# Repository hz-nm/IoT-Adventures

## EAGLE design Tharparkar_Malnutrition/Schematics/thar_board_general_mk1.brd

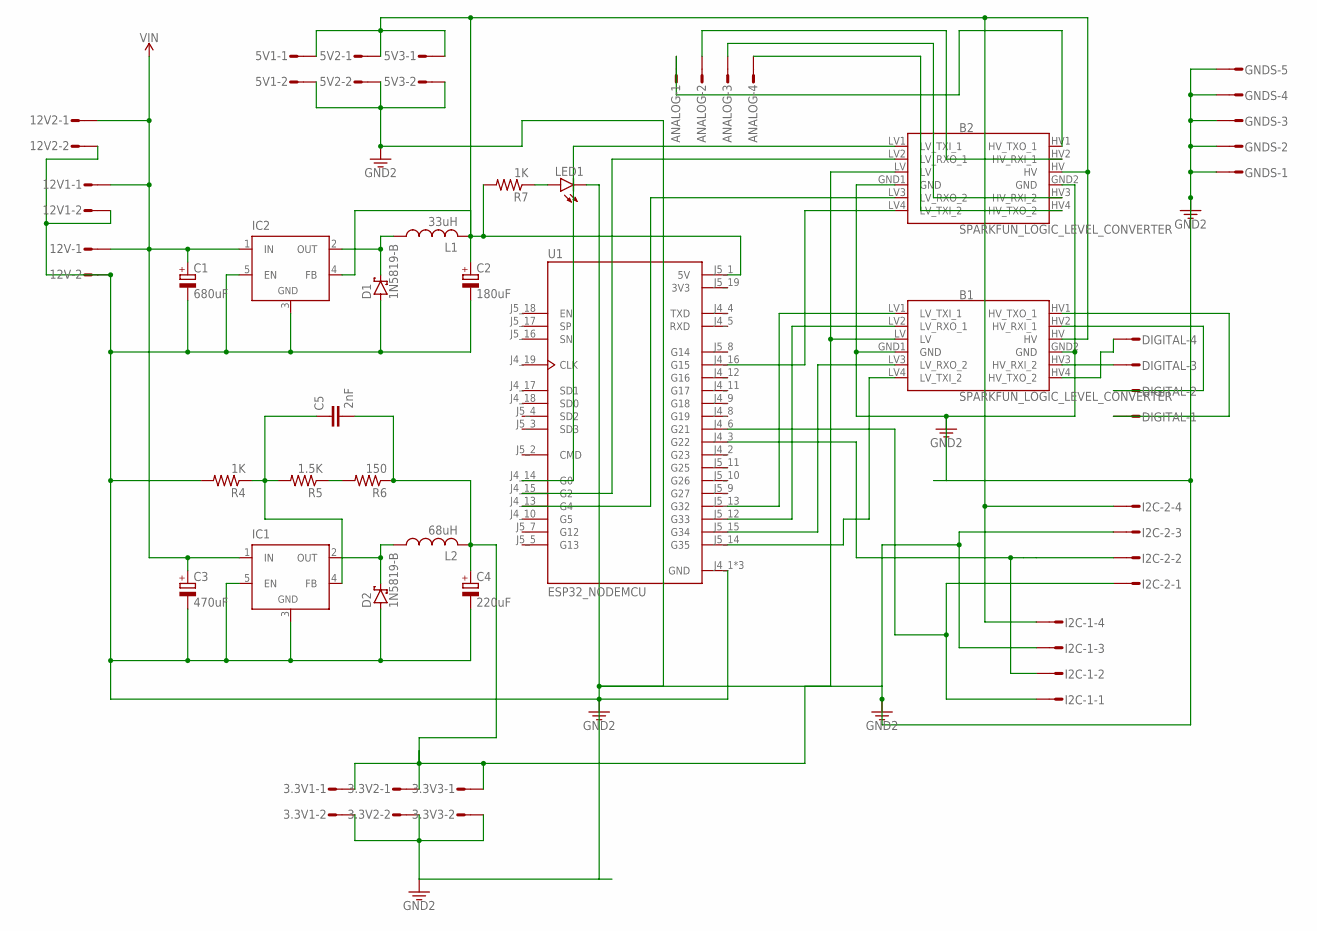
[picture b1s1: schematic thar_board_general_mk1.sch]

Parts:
3.3V1, 3.3V2, 3.3V3, 5V1, 5V2, 5V3, 12V, 12V1, 12V2: L02P
ANALOG: L04P
B1, B2: SPARKFUN_LOGIC_LEVEL_CONVERTER
C1: 680uF; E2,5-7
C2: 180uF; E2,5-7
C3: 470uF; E2,5-7
C4: 220uF; E2,5-7
C5: 2nF; C025-025X050
D1, D2: 1N5819-B; DO41-7.6
DIGITAL: L04P
GNDS: L05P
I2C-1, I2C-2: L04P
IC1, IC2: LM2596TH; TO220-52
L1: 33uH; TFI0410
L2: 68uH; TFI0410
LED1: LED3MM
R4, R7: 1K; 0207/10
R5: 1.5K; 0207/10
R6: 150; 0207/10
U1: ESP32_NODEMCU; MODULE_ESP32_NODEMCU

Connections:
3V3: U1.J5_19 (3V3)
5V: 5V1.1, 5V2.1, 5V3.1, B1.HV, B2.HV, C2.+, I2C-1.4, I2C-2.4, IC2.4 (FB), L1.2, R7.2, U1.J5_1 (5V)
5V1: 3.3V1.1, 3.3V2.1, 3.3V3.1, B1.LV, B2.LV, C4.+, C5.2, L2.2, R6.1
DLETE: B2.LV1 (LV_TXI_1), U1.J4_14 (G0)
GND: 3.3V1.2, 3.3V2.2, 3.3V3.2, 5V1.2, 5V2.2, 5V3.2, 12V.2, 12V1.2, 12V2.2, B1.GND1 (GND), B1.GND2 (GND), B2.GND1 (GND), B2.GND2 (GND), C1.-, C2.-, C3.-, C4.-, D1.A, D2.A, GNDS.1, GNDS.2, GNDS.3, GNDS.4, GNDS.5, I2C-1.3, I2C-2.3, IC1.3 (GND), IC1.5 (EN), IC2.3 (GND), IC2.5 (EN), LED1.K (C), R4.2, U1.J4_1 (GND), U1.J4_7 (GND), U1.J5_6 (GND)
unnamed: LED1.A, R7.1
unnamed: B2.LV4 (LV_TXI_2), U1.J4_16 (G15)
unnamed: B1.HV1 (HV_TXO_1), DIGITAL.1
unnamed: B2.LV2 (LV_RXO_1), U1.J4_15 (G2)
unnamed: D1.C, IC2.2 (OUT), L1.1
unnamed: B2.LV3 (LV_RXO_2), U1.J4_13 (G4)
unnamed: ANALOG.1, B2.HV1 (HV_TXO_1)
unnamed: D2.C, IC1.2 (OUT), L2.1
unnamed: ANALOG.4, B2.HV4 (HV_TXO_2)
unnamed: ANALOG.3, B2.HV3 (HV_RXI_2)
unnamed: ANALOG.2, B2.HV2 (HV_RXI_1)
unnamed: B1.LV1 (LV_TXI_1), U1.J5_13 (G32)
unnamed: C5.1, IC1.4 (FB), R4.1, R5.2
unnamed: B1.LV2 (LV_RXO_1), U1.J5_12 (G33)
unnamed: R5.1, R6.2
unnamed: B1.LV3 (LV_RXO_2), U1.J5_15 (G34)
unnamed: B1.LV4 (LV_TXI_2), U1.J5_14 (G35)
unnamed: B1.HV2 (HV_RXI_1), DIGITAL.2
unnamed: B1.HV3 (HV_RXI_2), DIGITAL.3
unnamed: B1.HV4 (HV_TXO_2), DIGITAL.4
SCL: I2C-1.2, I2C-2.2, U1.J4_3 (G22)
SDA: I2C-1.1, I2C-2.1, U1.J4_6 (G21)
VIN: 12V.1, 12V1.1, 12V2.1, C1.+, C3.+, IC1.1 (IN), IC2.1 (IN)

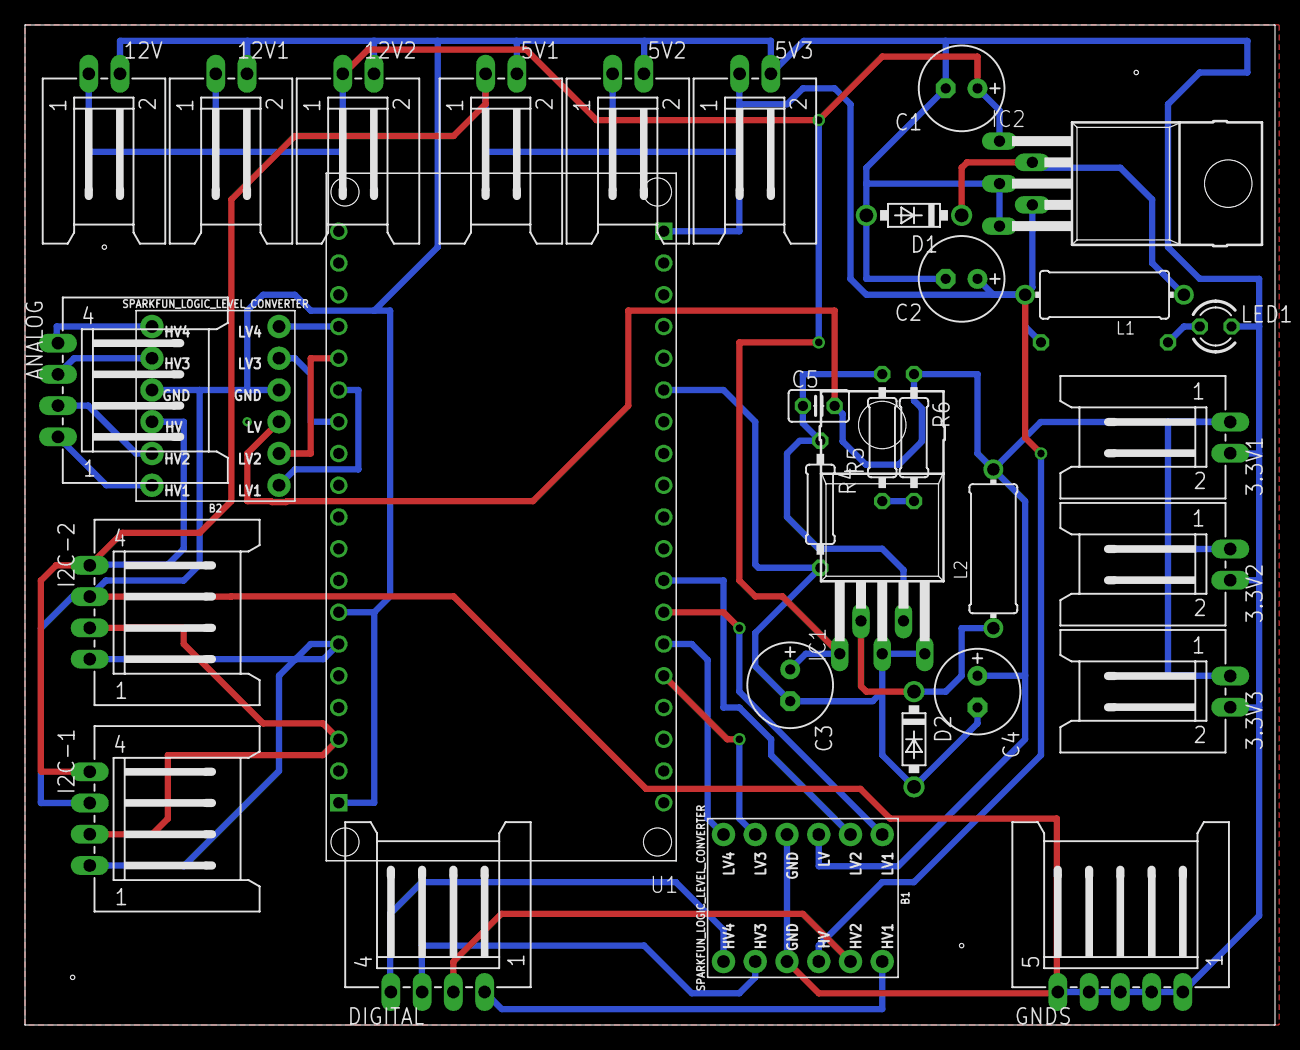
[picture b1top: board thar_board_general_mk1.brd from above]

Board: 2 copper layers, 100.0 x 80.0 mm, 33 parts (1 on the bottom side), 27 nets.

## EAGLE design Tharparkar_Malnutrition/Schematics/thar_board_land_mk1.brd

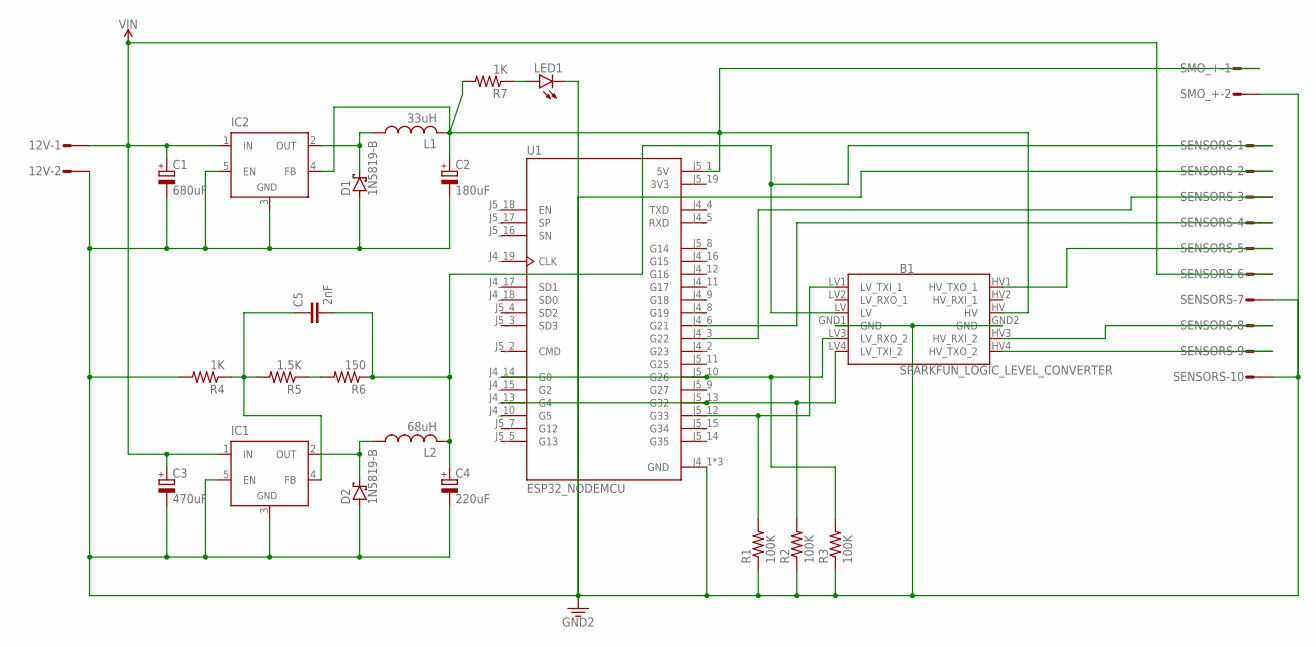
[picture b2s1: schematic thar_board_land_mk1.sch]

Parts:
12V: L02P
B1: SPARKFUN_LOGIC_LEVEL_CONVERTER
C1: 680uF; E2,5-7
C2: 180uF; E2,5-7
C3: 470uF; E2,5-7
C4: 220uF; E2,5-7
C5: 2nF; C025-025X050
D1, D2: 1N5819-B; DO41-7.6
IC1, IC2: LM2596TH; TO220-52
L1: 33uH; TFI0410
L2: 68uH; TFI0410
LED1: LED3MM
R1, R2, R3: 100K; 0207/10
R4, R7: 1K; 0207/10
R5: 1.5K; 0207/10
R6: 150; 0207/10
SENSORS: L10P
SMO_+: L02P
U1: ESP32_NODEMCU; MODULE_ESP32_NODEMCU

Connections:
3.3V: B1.LV, C4.+, C5.2, L2.2, R6.1, SENSORS.1
3V3: U1.J5_19 (3V3)
5V: B1.HV, C2.+, IC2.4 (FB), L1.2, R7.2, SMO_+.1, U1.J5_1 (5V)
GND: 12V.2, B1.GND1 (GND), B1.GND2 (GND), C1.-, C2.-, C3.-, C4.-, D1.A, D2.A, IC1.3 (GND), IC1.5 (EN), IC2.3 (GND), IC2.5 (EN), LED1.K (C), R1.1, R2.1, R3.1, R4.2, SENSORS.2, SENSORS.7, SENSORS.10, SMO_+.2, U1.J4_1 (GND), U1.J4_7 (GND), U1.J5_6 (GND)
unnamed: LED1.A, R7.1
unnamed: SENSORS.3, U1.J4_3 (G22)
unnamed: SENSORS.4, U1.J4_6 (G21)
unnamed: B1.HV3 (HV_RXI_2), SENSORS.8
unnamed: D1.C, IC2.2 (OUT), L1.1
unnamed: B1.HV4 (HV_TXO_2), SENSORS.9
unnamed: D2.C, IC1.2 (OUT), L2.1
unnamed: B1.HV1 (HV_TXO_1), SENSORS.5
unnamed: B1.LV1 (LV_TXI_1), R1.2, U1.J5_12 (G33)
unnamed: B1.LV3 (LV_RXO_2), R3.2, U1.J4_14 (G0), U1.J5_10 (G26)
unnamed: B1.LV4 (LV_TXI_2), R2.2, U1.J4_13 (G4), U1.J5_13 (G32)
unnamed: C5.1, IC1.4 (FB), R4.1, R5.2
unnamed: R5.1, R6.2
VIN: 12V.1, C1.+, C3.+, IC1.1 (IN), IC2.1 (IN), SENSORS.6

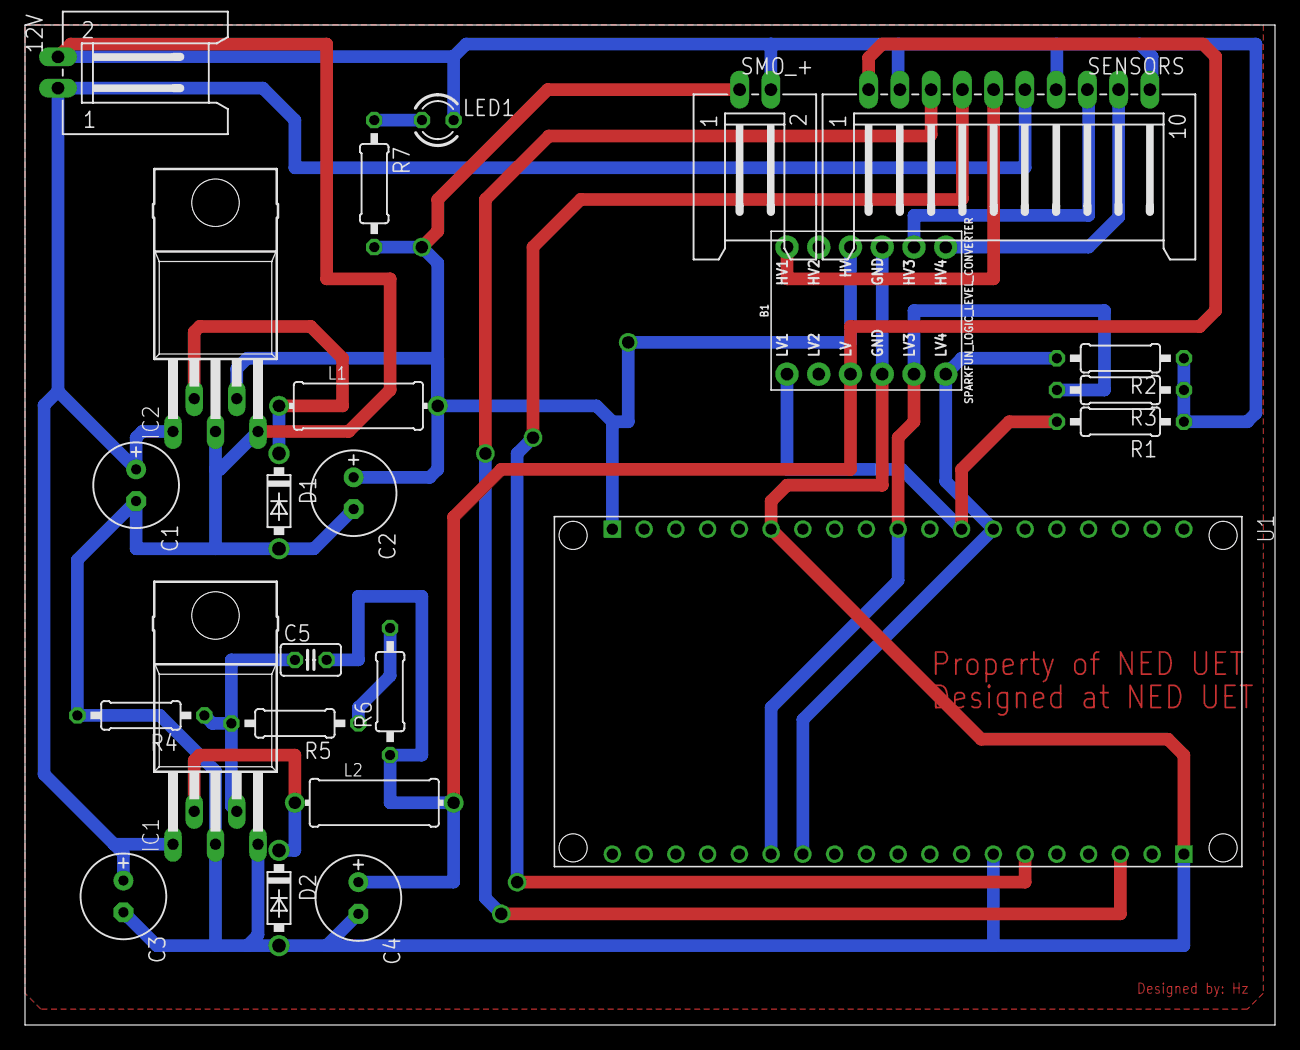
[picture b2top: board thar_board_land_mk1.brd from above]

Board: 2 copper layers, 100.0 x 80.0 mm, 24 parts (0 on the bottom side), 17 nets.

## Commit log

2023-06-22 Adventures in the world of Internet of Things

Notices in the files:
parts and their libraries:
SparkFun-Boards: Licensing: Creative Commons ShareAlike 4.0 International - https://creativecommons.org/licenses/by-sa/4.0
